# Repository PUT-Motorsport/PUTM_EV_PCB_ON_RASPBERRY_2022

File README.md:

# PUTM_EV_PCB_ON_RASPBERRY_2022

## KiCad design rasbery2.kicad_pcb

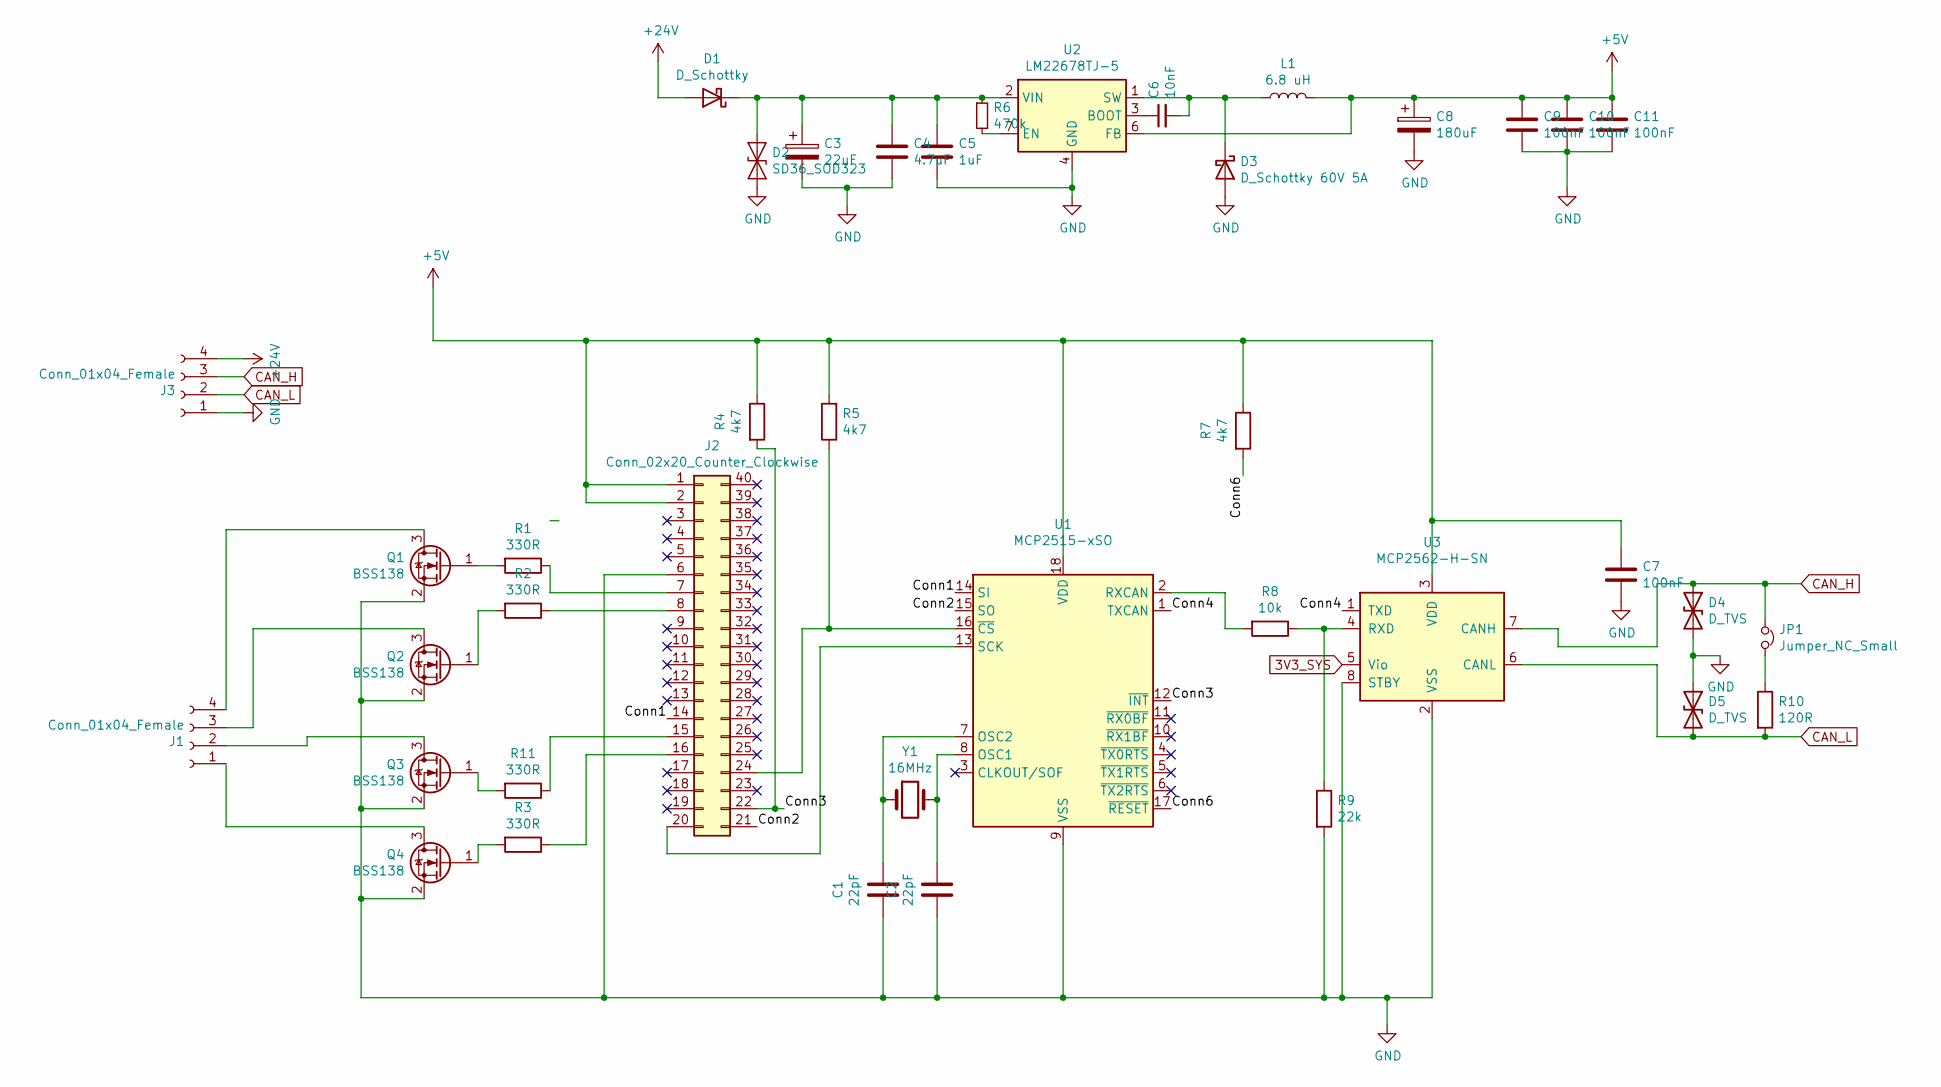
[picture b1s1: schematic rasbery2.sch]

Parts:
C1, C2: 22pF; C_0805_2012Metric
C3: 22uF; CP_Elec_6.3x5.8
C4: 4.7uF; C_0603_1608Metric
C5: 1uF; C_0603_1608Metric
C6: 10nF; C_0603_1608Metric
C7: 100nF; C_0805_2012Metric
C8: 180uF; C_Radial_D12.5mm_H20.0mm_P5.00mm
C9, C10, C11: 100nF; C_0603_1608Metric
D1: D_Schottky; D_SOD-123F
D2: SD36_SOD323; D_SOD-323
D3: D_Schottky 60V 5A; D_SOD-128
D4, D5: D_TVS; D_SMA
J1, J3: Conn_01x04_Female; TerminalBlock_MetzConnect_Type086_RT03404HBLC_1x04_P3.81mm_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
J2: Conn_02x20_Counter_Clockwise; PinHeader_2x20_P2.54mm_Vertical
JP1: Jumper_NC_Small; SolderJumper-3_P1.3mm_Bridged12_RoundedPad1.0x1.5mm_NumberL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
L1: 6.8 uH; L_Taiyo-Yuden_NR-30xx
Q1, Q2, Q3, Q4: BSS138; SOT-23
R1, R2, R3, R11: 330R; R_0805_2012Metric
R4, R5, R7: 4k7; R_0805_2012Metric
R6: 470k; R_0603_1608Metric
R8: 10k; R_0805_2012Metric
R9: 22k; R_0805_2012Metric
R10: 120R; R_0805_2012Metric
U1: MCP2515-xSO; SOIC-18W_7.5x11.6mm_P1.27mm
U2: LM22678TJ-5; TO-263-7_TabPin8
U3: MCP2562-H-SN; SOIC-8_3.9x4.9mm_P1.27mm
Y1: 16MHz; Crystal_AT310_D3.0mm_L10.0mm_Vertical

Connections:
3V3_SYS: U3.5 (Vio)
+5V: C7.1, C8.1, C9.1, C10.1, C11.1, J2.1, J2.2, L1.2, R4.1, R5.2, R7.1, U1.18 (VDD), U2.6 (FB), U3.3 (VDD)
+24V: D1.2 (A), J3.4
/Conn1: J2.14, U1.14 (SI)
/Conn2: J2.21, U1.15 (SO)
/Conn3: J2.22, R4.2, U1.12 (~INT)
/Conn4: U1.1 (TXCAN), U3.1 (TXD)
/Conn6: R7.2, U1.17 (~RESET)
CAN_H: D4.1 (A1), J3.3, JP1.1, U3.7 (CANH)
CAN_L: D5.2 (A2), J3.2, R10.2, U3.6 (CANL)
GND: C1.2, C2.2, C3.2, C4.2, C5.2, C7.2, C8.2, C9.2, C10.2, C11.2, D2.1 (A1), D3.2 (A), D4.2 (A2), D5.1 (A1), J2.6, J3.1, Q1.2 (S), Q2.2 (S), Q3.2 (S), Q4.2 (S), R9.2, U1.9 (VSS), U2.4 (GND), U2.8 (GND), U3.2 (VSS), U3.8 (STBY)
unnamed: C1.1, U1.7 (OSC2), Y1.1
unnamed: C2.1, U1.8 (OSC1), Y1.2
unnamed: C3.1, C4.1, C5.1, D1.1 (K), D2.2 (A2), R6.1, U2.2 (VIN)
unnamed: C6.1, U2.3 (BOOT)
unnamed: C6.2, D3.1 (K), L1.1, U2.1 (SW)
unnamed: J1.1, Q4.3 (D)
unnamed: J1.2, Q3.3 (D)
unnamed: J1.3, Q2.3 (D)
unnamed: J1.4, Q1.3 (D)
unnamed: J2.7, R1.1
unnamed: J2.8, R2.1
unnamed: J2.15, R11.1
unnamed: J2.16, R3.1
unnamed: J2.20, U1.13 (SCK)
unnamed: J2.24, R5.1, U1.16 (~CS)
unnamed: JP1.2, R10.1
unnamed: Q1.1 (G), R1.2
unnamed: Q2.1 (G), R2.2
unnamed: Q3.1 (G), R11.2
unnamed: Q4.1 (G), R3.2
unnamed: R6.2, U2.7 (EN)
unnamed: R8.1, R9.1, U3.4 (RXD)
unnamed: R8.2, U1.2 (RXCAN)

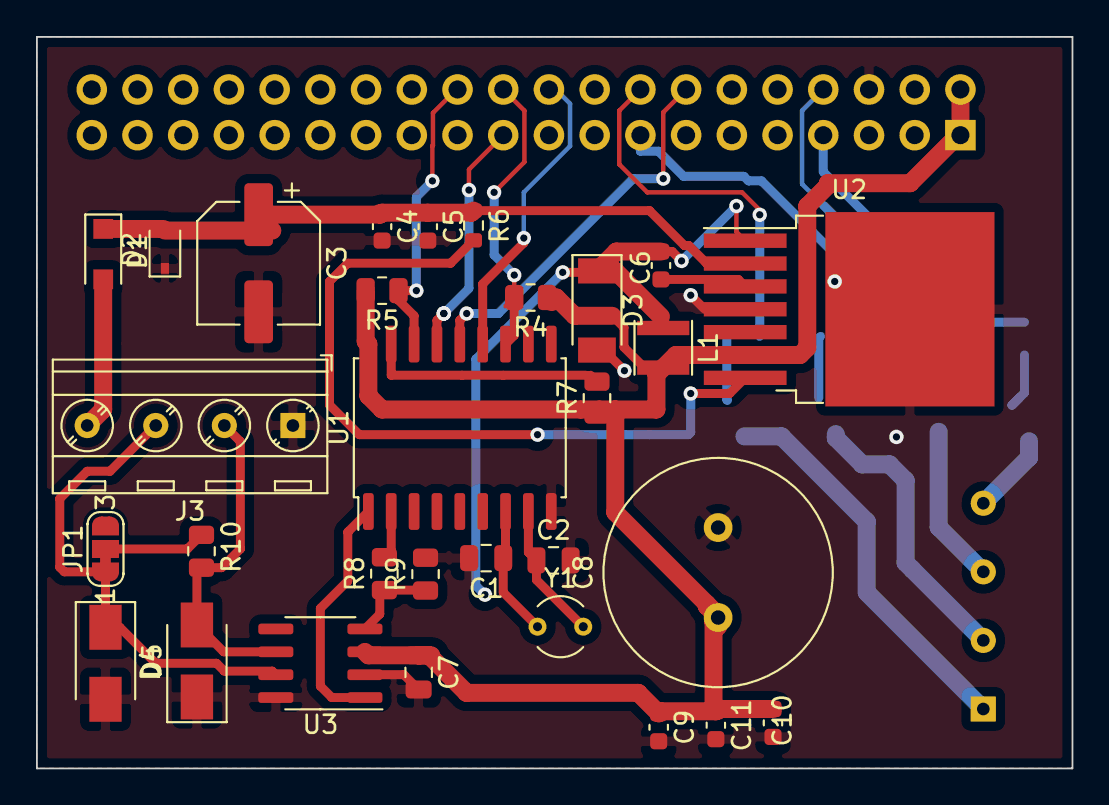
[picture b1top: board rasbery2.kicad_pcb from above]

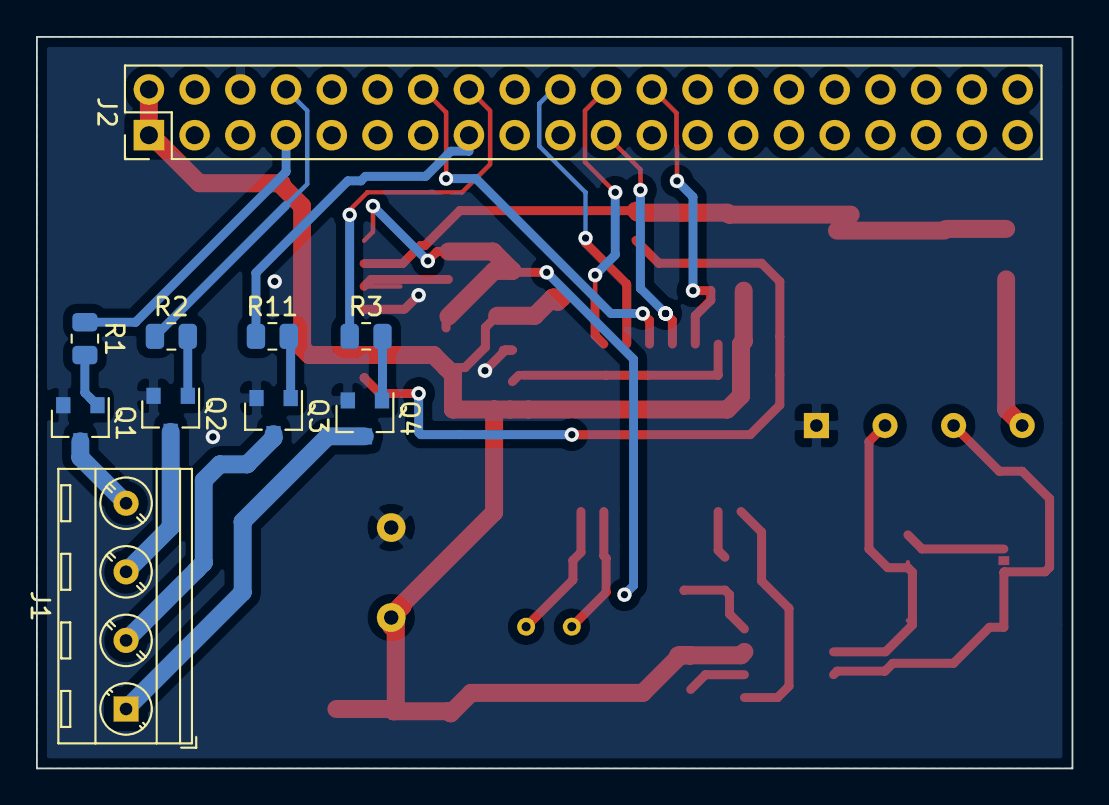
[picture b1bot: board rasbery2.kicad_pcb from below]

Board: 2 copper layers, 57.5 x 40.6 mm, 40 parts (10 on the bottom side), 33 nets.
